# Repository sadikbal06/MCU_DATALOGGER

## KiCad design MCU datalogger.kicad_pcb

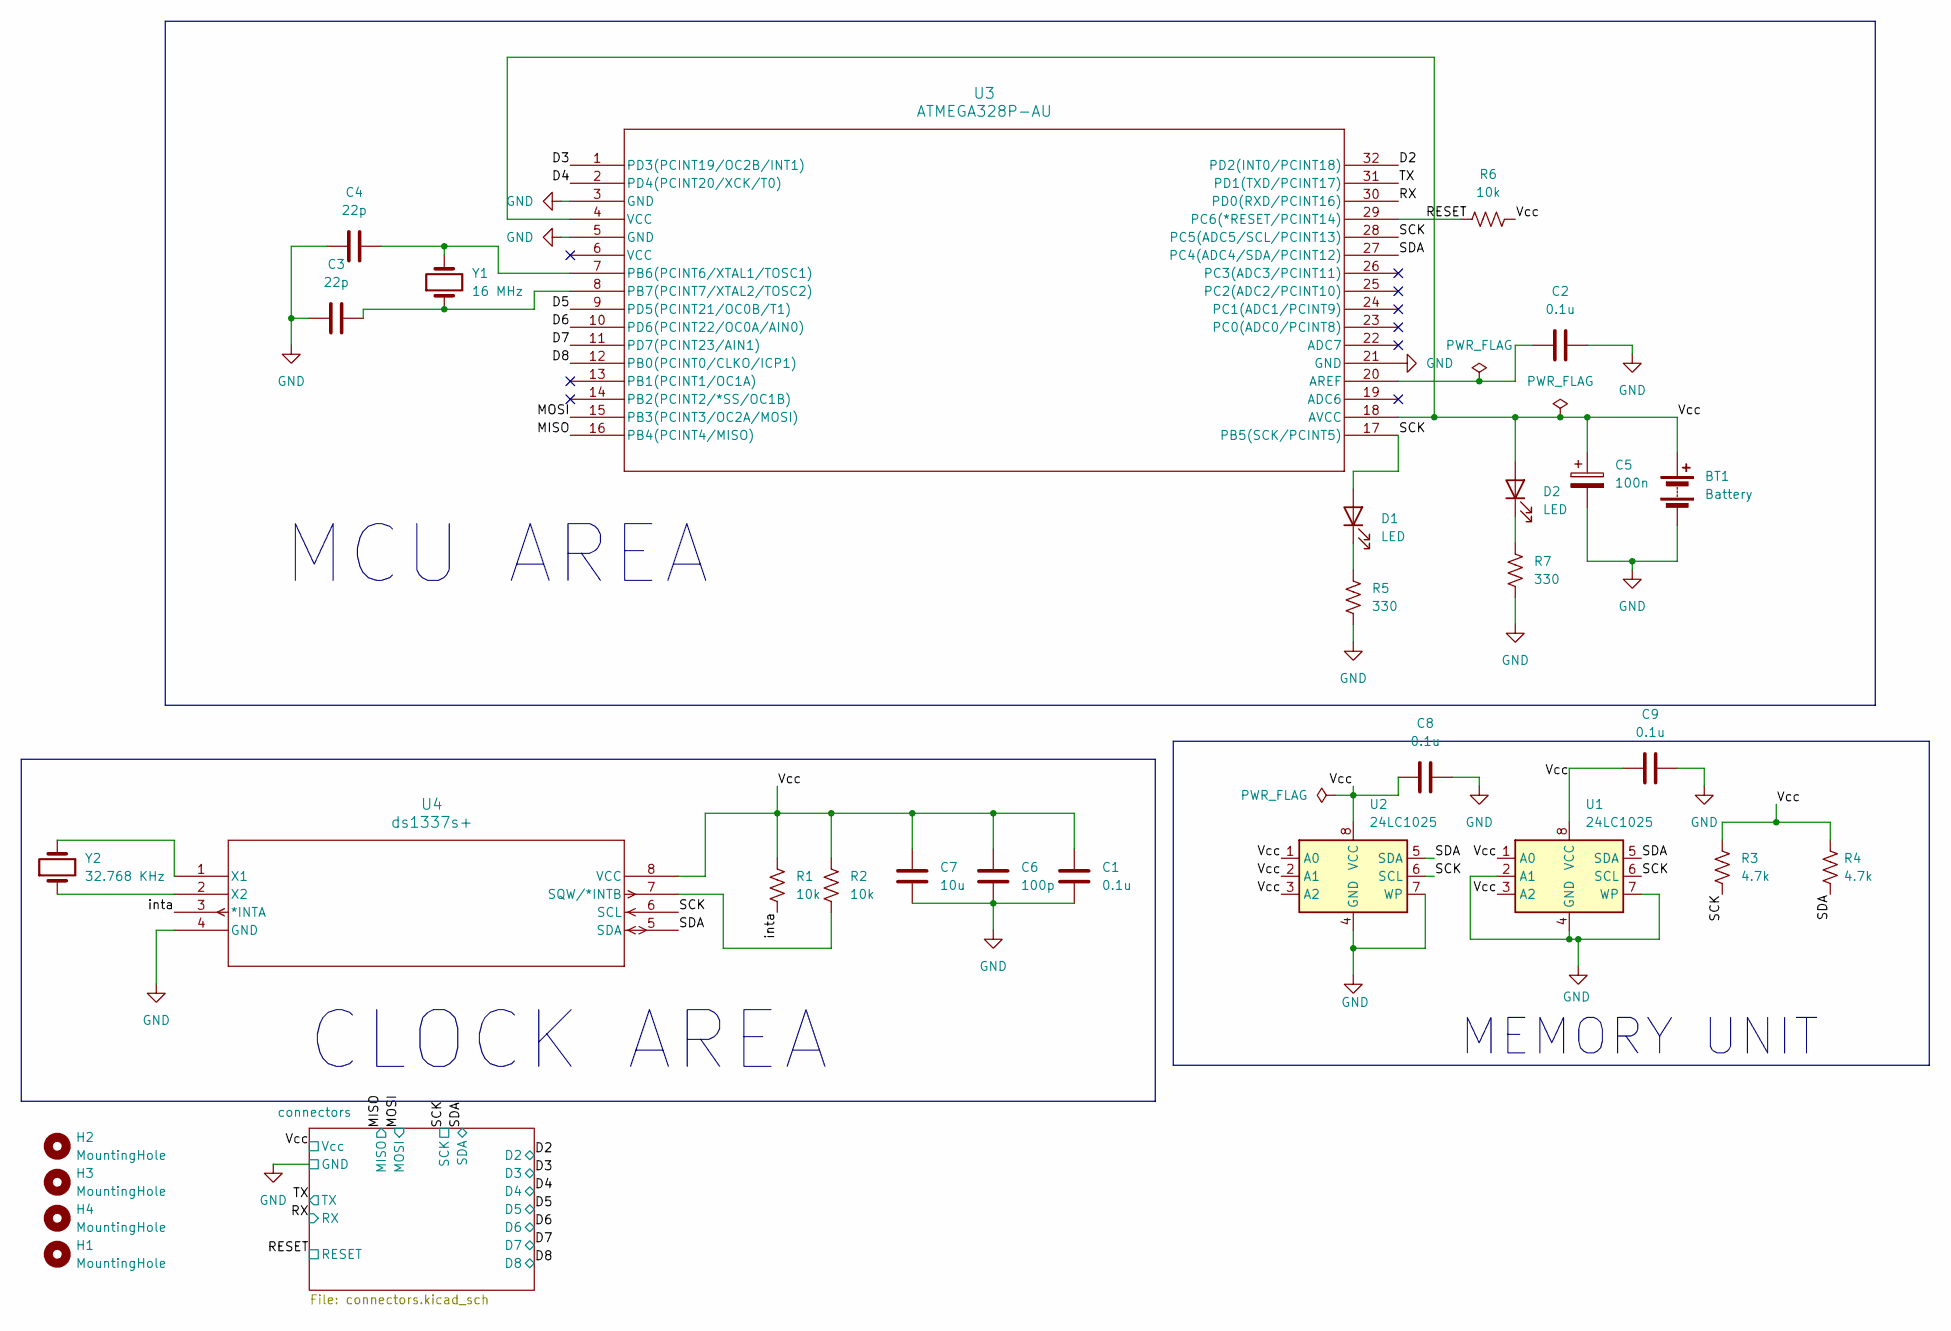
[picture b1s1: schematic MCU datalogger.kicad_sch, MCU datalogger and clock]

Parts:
BT1: Battery; PinHeader_2x01_P2.54mm_Vertical
C1, C2, C8, C9: 0.1u; C_0805_2012Metric
C3, C4: 22p; C_0805_2012Metric
C5: 100n; C_0805_2012Metric
C6: 100p; C_0805_2012Metric
C7: 10u; C_0805_2012Metric
D1, D2: LED; LED_0805_2012Metric
H1, H2, H3, H4: MountingHole; MountingHole_2.1mm
R1, R2, R6: 10k; R_0805_2012Metric
R3, R4: 4.7k; R_0805_2012Metric
R5, R7: 330; R_0805_2012Metric
U1, U2: 24LC1025; SOIC-8_3.9x4.9mm_P1.27mm
U3: ATMEGA328P-AU; TQFP32_32A_MCH
U4: ds1337s+; 21-0041B_8_MXM
Y1: 16 MHz; Crystal_SMD_5032-2Pin_5.0x3.2mm_HandSoldering
Y2: 32.768 KHz; Crystal_SMD_5032-2Pin_5.0x3.2mm_HandSoldering

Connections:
/D2: U3.32 (PD2(INT0/PCINT18)); also elsewhere on the board
/D3: U3.1 (PD3(PCINT19/OC2B/INT1)); also elsewhere on the board
/D4: U3.2 (PD4(PCINT20/XCK/T0)); also elsewhere on the board
/D5: U3.9 (PD5(PCINT21/OC0B/T1)); also elsewhere on the board
/D6: U3.10 (PD6(PCINT22/OC0A/AIN0)); also elsewhere on the board
/D7: U3.11 (PD7(PCINT23/AIN1)); also elsewhere on the board
/D8: U3.12 (PB0(PCINT0/CLKO/ICP1)); also elsewhere on the board
/MISO: U3.16 (PB4(PCINT4/MISO)); also elsewhere on the board
/MOSI: U3.15 (PB3(PCINT3/OC2A/MOSI)); also elsewhere on the board
/RESET: R6.1, U3.29 (PC6(*RESET/PCINT14)); also elsewhere on the board
/RX: U3.30 (PD0(RXD/PCINT16)); also elsewhere on the board
/SCK: D1.2 (A), R3.2, U1.6 (SCL), U2.6 (SCL), U3.17 (PB5(SCK/PCINT5)), U3.28 (PC5(ADC5/SCL/PCINT13)), U4.6 (SCL); also elsewhere on the board
/SDA: R4.2, U1.5 (SDA), U2.5 (SDA), U3.27 (PC4(ADC4/SDA/PCINT12)), U4.5 (SDA); also elsewhere on the board
/TX: U3.31 (PD1(TXD/PCINT17)); also elsewhere on the board
/Vcc: BT1.1 (+), C1.1, C5.1, C6.1, C7.1, C8.1, C9.1, D2.2 (A), R1.1, R2.1, R3.1, R4.1, R6.2, U1.1 (A0), U1.3 (A2), U1.8 (VCC), U2.1 (A0), U2.2 (A1), U2.3 (A2), U2.8 (VCC), U3.4 (VCC), U3.18 (AVCC), U4.8 (VCC); also elsewhere on the board
/inta: R1.2, U4.3 (*INTA)
GND: BT1.2 (-), C1.2, C2.2, C3.2, C4.1, C5.2, C6.2, C7.2, C8.2, C9.2, R5.2, R7.2, U1.2 (A1), U1.4 (GND), U1.7 (WP), U2.4 (GND), U2.7 (WP), U3.3 (GND), U3.5 (GND), U3.21 (GND), U4.4 (GND); also elsewhere on the board
unnamed: D1.1 (K), R5.1
unnamed: D2.1 (K), R7.1
unnamed: C2.1, U3.20 (AREF)
unnamed: C4.2, U3.7 (PB6(PCINT6/XTAL1/TOSC1)), Y1.2
unnamed: C3.1, U3.8 (PB7(PCINT7/XTAL2/TOSC2)), Y1.1
unnamed: R2.2, U4.7 (SQW/*INTB)
unnamed: U4.1 (X1), Y2.2
unnamed: U4.2 (X2), Y2.1

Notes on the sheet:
MCU AREA
MEMORY UNIT
CLOCK AREA

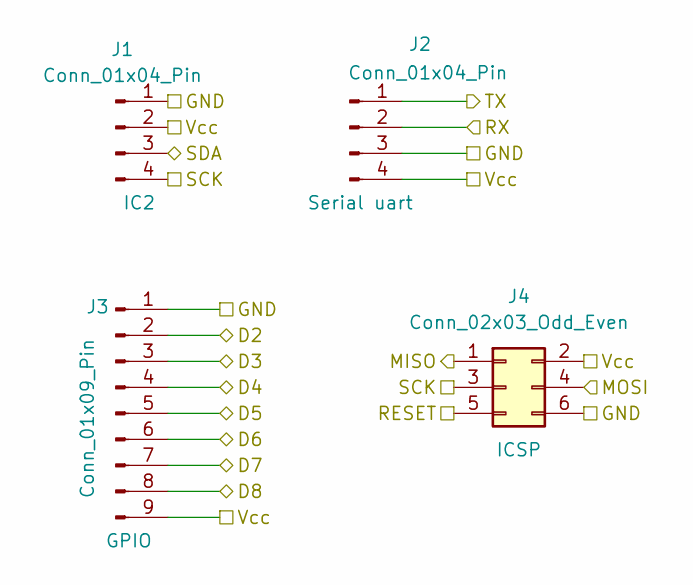
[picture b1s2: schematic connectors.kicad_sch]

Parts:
J1, J2: Conn_01x04_Pin; PinHeader_1x04_P2.54mm_Vertical
J3: Conn_01x09_Pin; PinHeader_1x09_P2.54mm_Vertical
J4: Conn_02x03_Odd_Even; PinHeader_2x03_P2.54mm_Vertical

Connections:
/D2: J3.2; also elsewhere on the board
/D3: J3.3; also elsewhere on the board
/D4: J3.4; also elsewhere on the board
/D5: J3.5; also elsewhere on the board
/D6: J3.6; also elsewhere on the board
/D7: J3.7; also elsewhere on the board
/D8: J3.8; also elsewhere on the board
/MISO: J4.1; also elsewhere on the board
/MOSI: J4.4; also elsewhere on the board
/RESET: J4.5; also elsewhere on the board
/RX: J2.2; also elsewhere on the board
/SCK: J1.4, J4.3; also elsewhere on the board
/SDA: J1.3; also elsewhere on the board
/TX: J2.1; also elsewhere on the board
/Vcc: J1.2, J2.4, J3.9, J4.2; also elsewhere on the board
GND: J1.1, J2.3, J3.1, J4.6; also elsewhere on the board

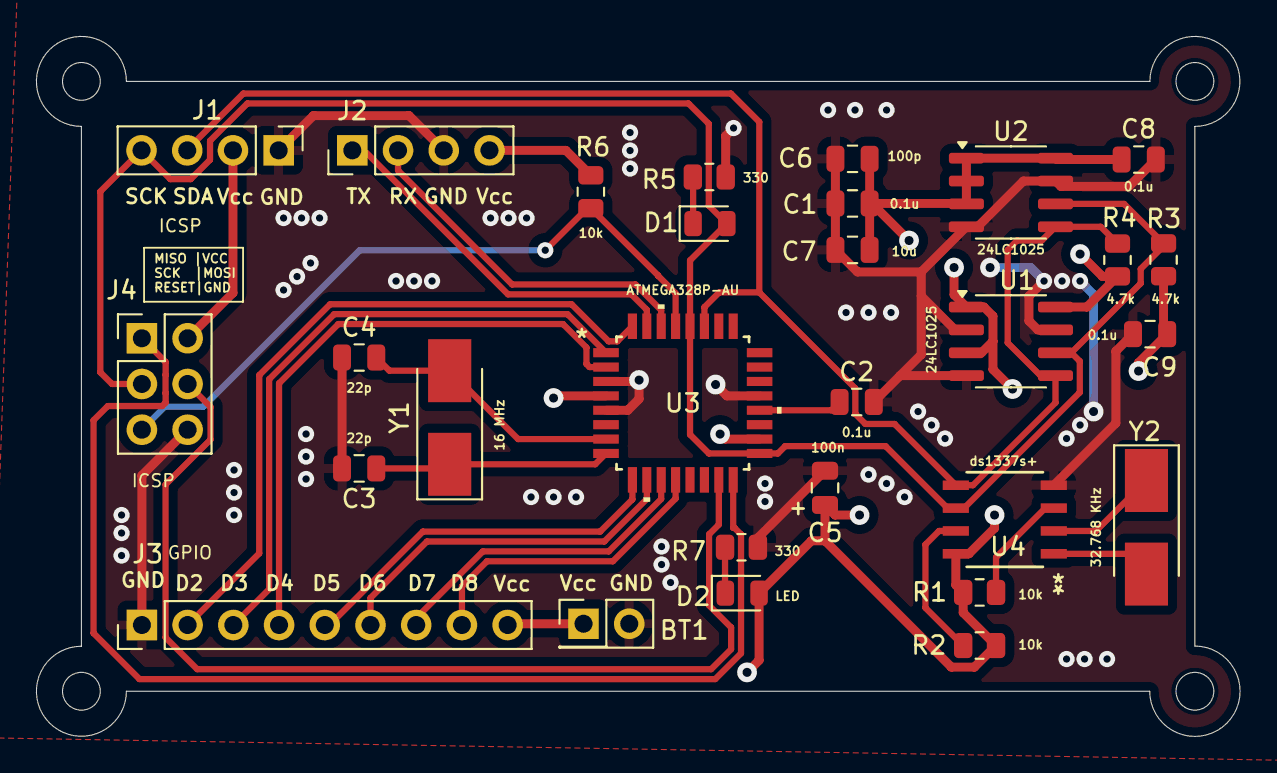
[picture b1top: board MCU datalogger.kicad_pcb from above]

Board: 4 copper layers, 66.9 x 38.9 mm, 33 parts (0 on the bottom side), 25 nets.

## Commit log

2025-08-24 ilk kayı
2025-09-08 2_layer_mcu_compleated_project
2025-09-08 ignored_files
2025-09-08 Compleated_4Layer_routing
2025-09-11 4 Layer Update for PCB
